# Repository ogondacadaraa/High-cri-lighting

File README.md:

# High quality lighting

A tunable white LED light. One driver board runs two 100×100 mm aluminium LED boards, each with 96 warm and cold white LEDs, and the colour temperature and brightness are set from a phone or with two knobs.

Made in KiCad 10.

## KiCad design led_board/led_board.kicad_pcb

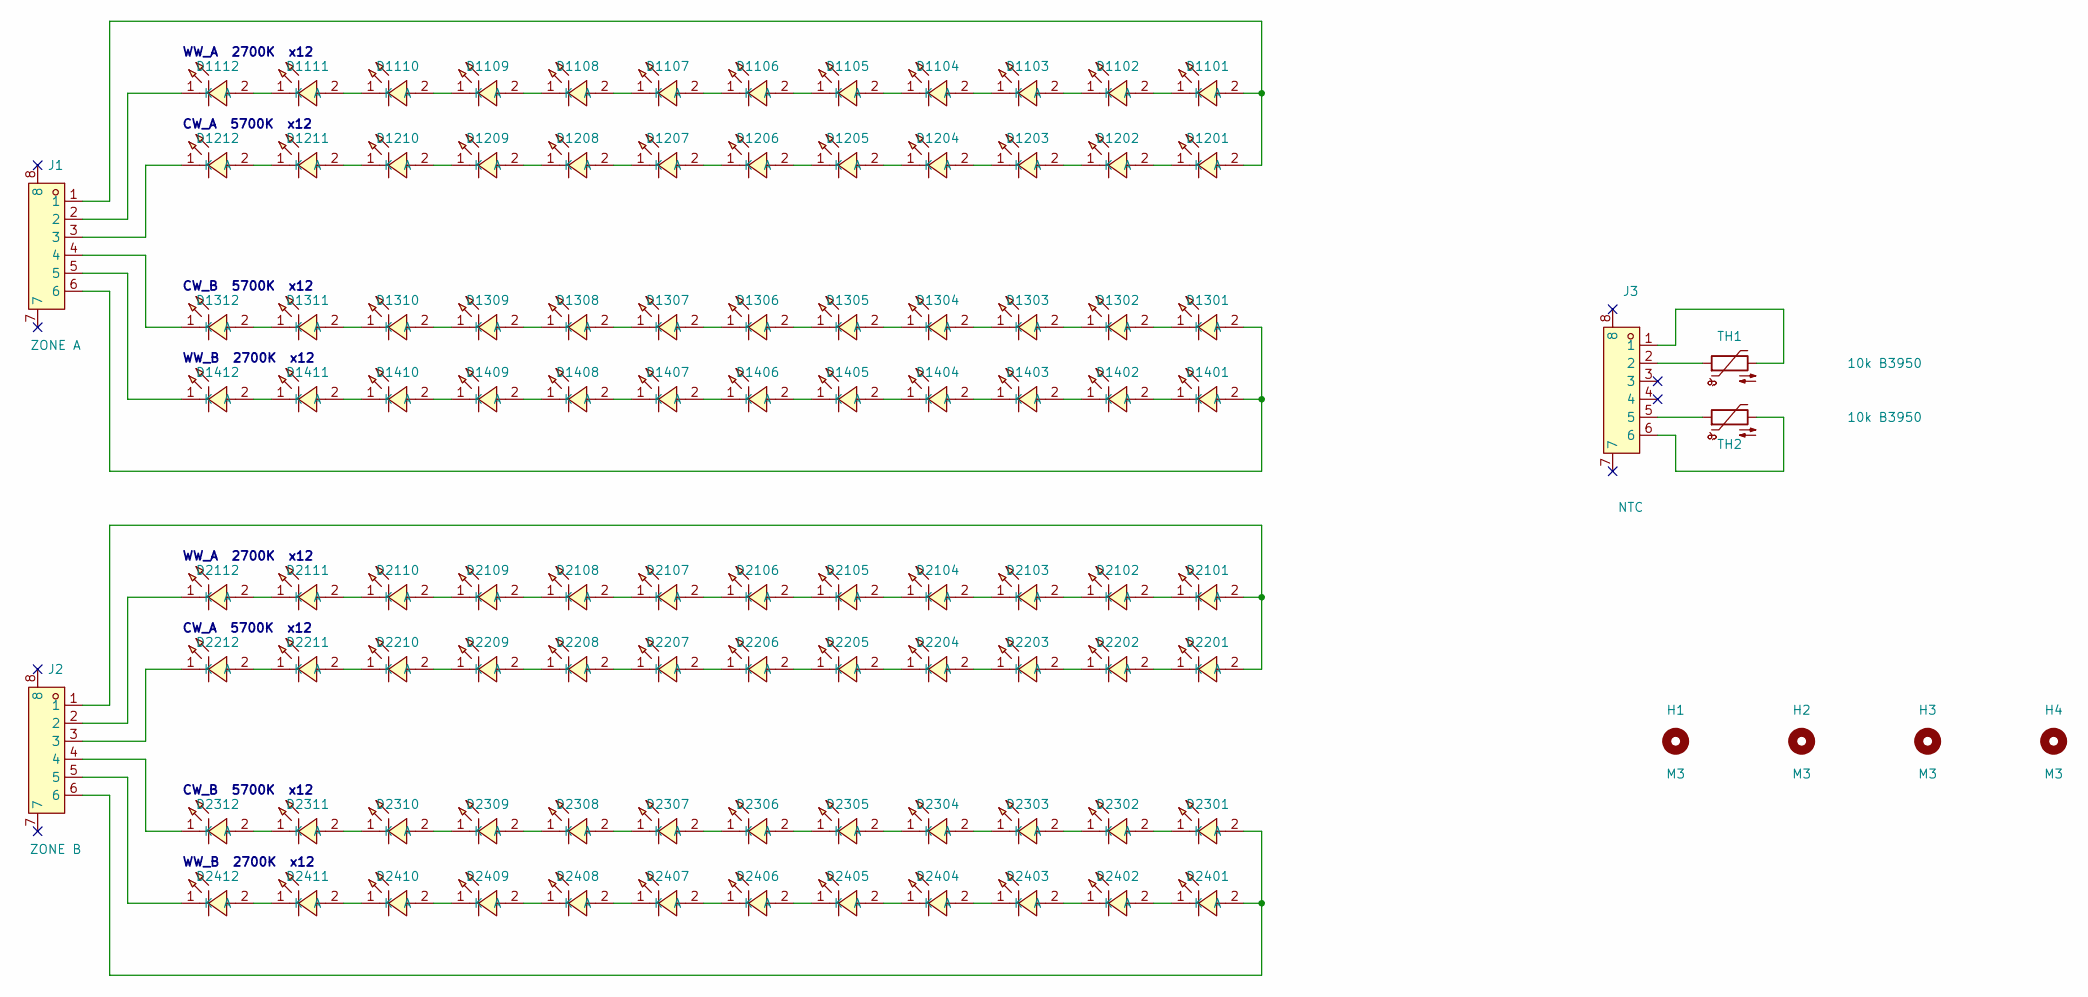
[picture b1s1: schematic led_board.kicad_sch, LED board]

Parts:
D1101, D1102, D1103, D1104, D1105, D1106, D1107, D1108, D1109, D1110, D1111, D1112, D1401, D1402, D1403, D1404, D1405, D1406, D1407, D1408, D1409, D1410, D1411, D1412, D2101, D2102, D2103, D2104, D2105, D2106, D2107, D2108, D2109, D2110, D2111, D2112, D2401, D2402, D2403, D2404, D2405, D2406, D2407, D2408, D2409, D2410, D2411, D2412: GW JTLMS3.GM-G3G7-XX58-1-60-R33 2700K; LED-SMD_L3.5-W2.8-RD; MPN GW JTLMS3.GM-G3G7-XX58-1-60-R33
D1201, D1202, D1203, D1204, D1205, D1206, D1207, D1208, D1209, D1210, D1211, D1212, D1301, D1302, D1303, D1304, D1305, D1306, D1307, D1308, D1309, D1310, D1311, D1312, D2201, D2202, D2203, D2204, D2205, D2206, D2207, D2208, D2209, D2210, D2211, D2212, D2301, D2302, D2303, D2304, D2305, D2306, D2307, D2308, D2309, D2310, D2311, D2312: GW JTLPS1.EM-KMLN-XX52-1-C 5700K; LED-SMD_L3.5-W2.8-RD; MPN GW JTLPS1.EM-KMLN-XX52-1-C; LCSC Part C5210961
H1, H2, H3, H4: M3; MountingHole_3.2mm_M3
J1: ZONE A; CONN-SMD_LQ-XH-6PWT; MPN LQ-XH-6PWT; LCSC Part C54618890
J2: ZONE B; CONN-SMD_LQ-XH-6PWT; MPN LQ-XH-6PWT; LCSC Part C54618890
J3: NTC; CONN-SMD_LQ-XH-6PWT; MPN LQ-XH-6PWT; LCSC Part C54618890
TH1, TH2: 10k B3950; R_0805_2012Metric

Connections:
unnamed: D1101.2 (A), D1201.2 (A), J1.1
unnamed: D1101.1 (K), D1102.2 (A)
unnamed: D1102.1 (K), D1103.2 (A)
unnamed: D1103.1 (K), D1104.2 (A)
unnamed: D1104.1 (K), D1105.2 (A)
unnamed: D1105.1 (K), D1106.2 (A)
unnamed: D1106.1 (K), D1107.2 (A)
unnamed: D1107.1 (K), D1108.2 (A)
unnamed: D1108.1 (K), D1109.2 (A)
unnamed: D1109.1 (K), D1110.2 (A)
unnamed: D1110.1 (K), D1111.2 (A)
unnamed: D1111.1 (K), D1112.2 (A)
unnamed: D1112.1 (K), J1.2
unnamed: D1201.1 (K), D1202.2 (A)
unnamed: D1202.1 (K), D1203.2 (A)
unnamed: D1203.1 (K), D1204.2 (A)
unnamed: D1204.1 (K), D1205.2 (A)
unnamed: D1205.1 (K), D1206.2 (A)
unnamed: D1206.1 (K), D1207.2 (A)
unnamed: D1207.1 (K), D1208.2 (A)
unnamed: D1208.1 (K), D1209.2 (A)
unnamed: D1209.1 (K), D1210.2 (A)
unnamed: D1210.1 (K), D1211.2 (A)
unnamed: D1211.1 (K), D1212.2 (A)
unnamed: D1212.1 (K), J1.3
unnamed: D1301.2 (A), D1401.2 (A), J1.6
unnamed: D1301.1 (K), D1302.2 (A)
unnamed: D1302.1 (K), D1303.2 (A)
unnamed: D1303.1 (K), D1304.2 (A)
unnamed: D1304.1 (K), D1305.2 (A)
unnamed: D1305.1 (K), D1306.2 (A)
unnamed: D1306.1 (K), D1307.2 (A)
unnamed: D1307.1 (K), D1308.2 (A)
unnamed: D1308.1 (K), D1309.2 (A)
unnamed: D1309.1 (K), D1310.2 (A)
unnamed: D1310.1 (K), D1311.2 (A)
unnamed: D1311.1 (K), D1312.2 (A)
unnamed: D1312.1 (K), J1.4
unnamed: D1401.1 (K), D1402.2 (A)
unnamed: D1402.1 (K), D1403.2 (A)
unnamed: D1403.1 (K), D1404.2 (A)
unnamed: D1404.1 (K), D1405.2 (A)
unnamed: D1405.1 (K), D1406.2 (A)
unnamed: D1406.1 (K), D1407.2 (A)
unnamed: D1407.1 (K), D1408.2 (A)
unnamed: D1408.1 (K), D1409.2 (A)
unnamed: D1409.1 (K), D1410.2 (A)
unnamed: D1410.1 (K), D1411.2 (A)
unnamed: D1411.1 (K), D1412.2 (A)
unnamed: D1412.1 (K), J1.5
unnamed: D2101.2 (A), D2201.2 (A), J2.1
unnamed: D2101.1 (K), D2102.2 (A)
unnamed: D2102.1 (K), D2103.2 (A)
unnamed: D2103.1 (K), D2104.2 (A)
unnamed: D2104.1 (K), D2105.2 (A)
unnamed: D2105.1 (K), D2106.2 (A)
unnamed: D2106.1 (K), D2107.2 (A)
unnamed: D2107.1 (K), D2108.2 (A)
unnamed: D2108.1 (K), D2109.2 (A)
unnamed: D2109.1 (K), D2110.2 (A)
unnamed: D2110.1 (K), D2111.2 (A)
unnamed: D2111.1 (K), D2112.2 (A)
unnamed: D2112.1 (K), J2.2
unnamed: D2201.1 (K), D2202.2 (A)
unnamed: D2202.1 (K), D2203.2 (A)
unnamed: D2203.1 (K), D2204.2 (A)
unnamed: D2204.1 (K), D2205.2 (A)
unnamed: D2205.1 (K), D2206.2 (A)
unnamed: D2206.1 (K), D2207.2 (A)
unnamed: D2207.1 (K), D2208.2 (A)
unnamed: D2208.1 (K), D2209.2 (A)
unnamed: D2209.1 (K), D2210.2 (A)
unnamed: D2210.1 (K), D2211.2 (A)
unnamed: D2211.1 (K), D2212.2 (A)
unnamed: D2212.1 (K), J2.3
unnamed: D2301.2 (A), D2401.2 (A), J2.6
unnamed: D2301.1 (K), D2302.2 (A)
unnamed: D2302.1 (K), D2303.2 (A)
unnamed: D2303.1 (K), D2304.2 (A)
unnamed: D2304.1 (K), D2305.2 (A)
unnamed: D2305.1 (K), D2306.2 (A)
unnamed: D2306.1 (K), D2307.2 (A)
unnamed: D2307.1 (K), D2308.2 (A)
unnamed: D2308.1 (K), D2309.2 (A)
unnamed: D2309.1 (K), D2310.2 (A)
unnamed: D2310.1 (K), D2311.2 (A)
unnamed: D2311.1 (K), D2312.2 (A)
unnamed: D2312.1 (K), J2.4
unnamed: D2401.1 (K), D2402.2 (A)
unnamed: D2402.1 (K), D2403.2 (A)
unnamed: D2403.1 (K), D2404.2 (A)
unnamed: D2404.1 (K), D2405.2 (A)
unnamed: D2405.1 (K), D2406.2 (A)
unnamed: D2406.1 (K), D2407.2 (A)
unnamed: D2407.1 (K), D2408.2 (A)
unnamed: D2408.1 (K), D2409.2 (A)
unnamed: D2409.1 (K), D2410.2 (A)
unnamed: D2410.1 (K), D2411.2 (A)
unnamed: D2411.1 (K), D2412.2 (A)
unnamed: D2412.1 (K), J2.5
unnamed: J3.1, TH1.2
unnamed: J3.2, TH1.1
unnamed: J3.5, TH2.1
unnamed: J3.6, TH2.2

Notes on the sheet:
WW_A 2700K x12
CW_A 5700K x12
CW_B 5700K x12
WW_B 2700K x12

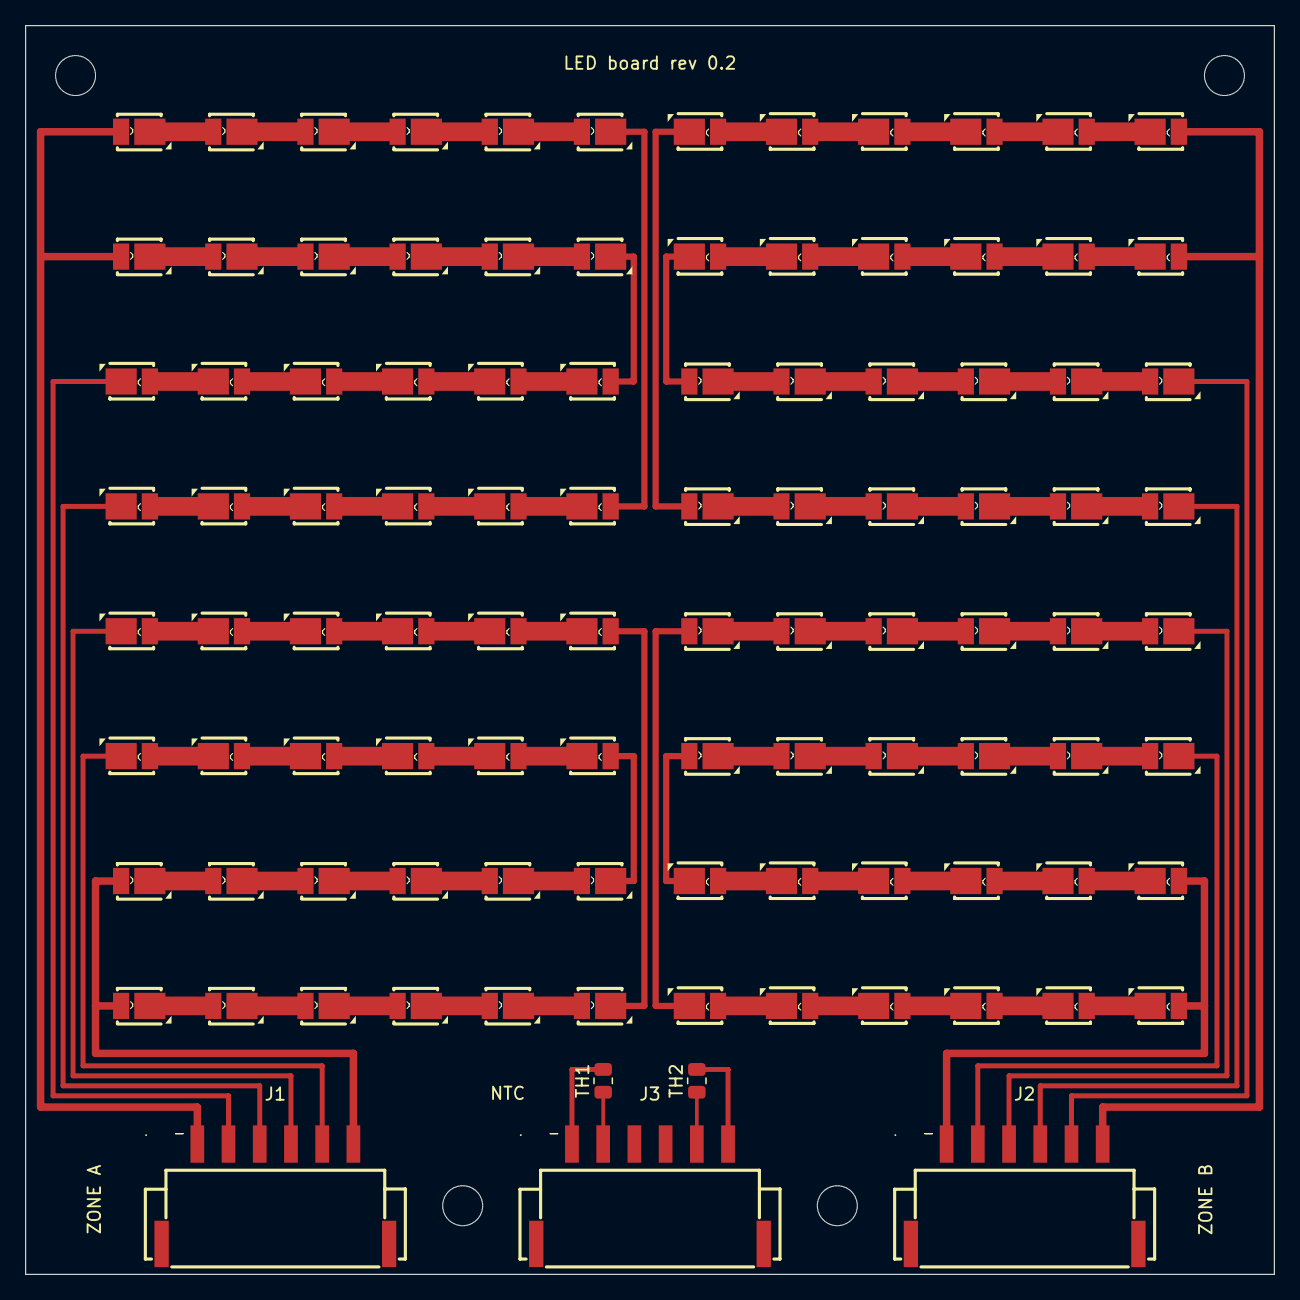
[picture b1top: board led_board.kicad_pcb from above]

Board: 2 copper layers, 100.0 x 100.0 mm, 105 parts (0 on the bottom side), 104 nets.
